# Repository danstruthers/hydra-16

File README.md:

## **Hydra 16**

A multitasking 65C02 computer and its operating system, HydraOS.

The Hydra-16's hardware gives each of 16 tasks its own 32K of RAM, zero page and stack included, with its own RAM and ROM bank selections, so a task switch is one register write.  HydraOS runs on it, Plan 9's way:
* **One kernel** in the BIOS ROM: a preemptive scheduler, one interrupt path, notes, memory and banks, and a jump table made from a specification.  Everything else is a module of the paged ROM, run in place in a task of its own.
* **A base to build on:** the kernel, a serial console driver, the kernel's devices and Woz's monitor are the base (`base/`), which HydraOS is built on and which boots on its own: [write an OS of your own](docs/09-programming/your-own-os.md) on it.
* **Everything a file:** devices are file servers (the console's windows, the disks and HydraFS, sound, GPIO and I2C, the clock, the Vera X, and `/pc`, a folder on the PC over the serial line), and each task has a namespace of its own, built by binds and mounts.
* **Shells and languages:** rc, Plan 9's shell, and the core tools; HyForth (Forth 2012), the login shell; hylang (danlang, a lisp); HyBASIC (QuickBASIC's kind, every number exact); SDKs for C (cc65) and assembly, and `as`, an assembler on the Hydra itself.
* **Tools:** a screen editor (`edit`), a debugger (`db`), a song player that plays ZSM songs and compiles scores as it plays.

The code is built with **cc65** (https://cc65.github.io/), and the board is designed in **KiCad 9** (https://www.kicad.org).

### **Quick start**

```
cd base
node build.js                      the base alone: the kernel, ser, kdev, the monitor (bin/bios_*.bin, bin/prom0.bin)
node sim/run.js -i                 its monitor in your terminal (Ctrl-A x quits)

cd ../reborn
node build.js                      build HydraOS (needs Node.js and cc65): bin/bios_*.bin, bin/prom0.bin ...
node sim/run.js -i                 use the Hydra in your terminal, in the emulator (Ctrl-A x quits)
node sim/web.js                    the emulator in a browser: one file, bin/hydra-16.html, to open (in Git: no
                                   Node.js needed to use it)
node sim/test.js                   the regression tests
```

The ROM images are in Git (`reborn/bin/`) and on each GitHub release, so the chips can be programmed without a toolchain.

### **Documentation**

**[The Hydra-16 book](docs/README.md)** is everything, in order: what the machine is, the board and how to build it
(the parts, the layout, the quirks), the kernel and its calls, the drivers, the shell, the languages, the tools, the
emulator, and the programming guide.  It's also [one PDF](docs/hydra-16.pdf), to print.

| Chapter | |
| :------ | :- |
| [1. The Hydra-16 at a glance](docs/01-overview.md) | The ideas, the software in layers, and a first hour in the emulator |
| [2. The hardware](docs/02-hardware/README.md) | The architecture, the devices, the parts, building it, the layout, the quirks, the cards |
| [3. The base](docs/03-base/README.md) | The boot, the kernel, files and namespaces, the system calls, the monitor |
| [4. The drivers](docs/04-drivers/README.md) | The serial console, the kernel's devices, storage, sound, GPIO, video |
| [5. The shell: rc](docs/05-rc.md) | Plan 9's shell |
| [6. The languages](docs/06-languages/README.md) | HyForth, hylang, HyBASIC, and the numbers they share |
| [7. The tools](docs/07-tools.md) | The core tools, the editors, the debugger, the assembler and disassembler |
| [8. The emulator](docs/08-emulator.md) | The emulator, the build, the tests, the PC tools |
| [9. The programming guide](docs/09-programming/README.md) | Assembly, C, servers and drivers, libraries, your own OS, every system call |

How it was designed, and where it stands: [the plan and the design notes](docs/design/README.md).

### **Repository**

| Folder | What |
| :----- | :--- |
| `base/` | The base: the kernel (the BIOS ROM), the system calls' specification, the console driver `ser`, the kernel's devices `kdev`, the monitor `wozmon`, the assembly SDK's core, the board's emulator and the tests' runner |
| `reborn/` | HydraOS, on the base: its modules, the SDKs, the ROM disk, the SD card's image, its tests |
| `docs/` | The book (its chapters, `docs/build`: the tools that make its parts list, layout drawings, call reference and PDF), and the design notes (`docs/design`) |
| `board/` | KiCad schematics and PCBs: the main board, the memory daughter card, the bus breakout card, the Vera X's glue board |
| `old/` | The old system (the 1.8C line: `os_rom/`, its programs, emulator, build and documents), frozen at HydraOS 1.0; `node old/build.js test` still builds and tests it |

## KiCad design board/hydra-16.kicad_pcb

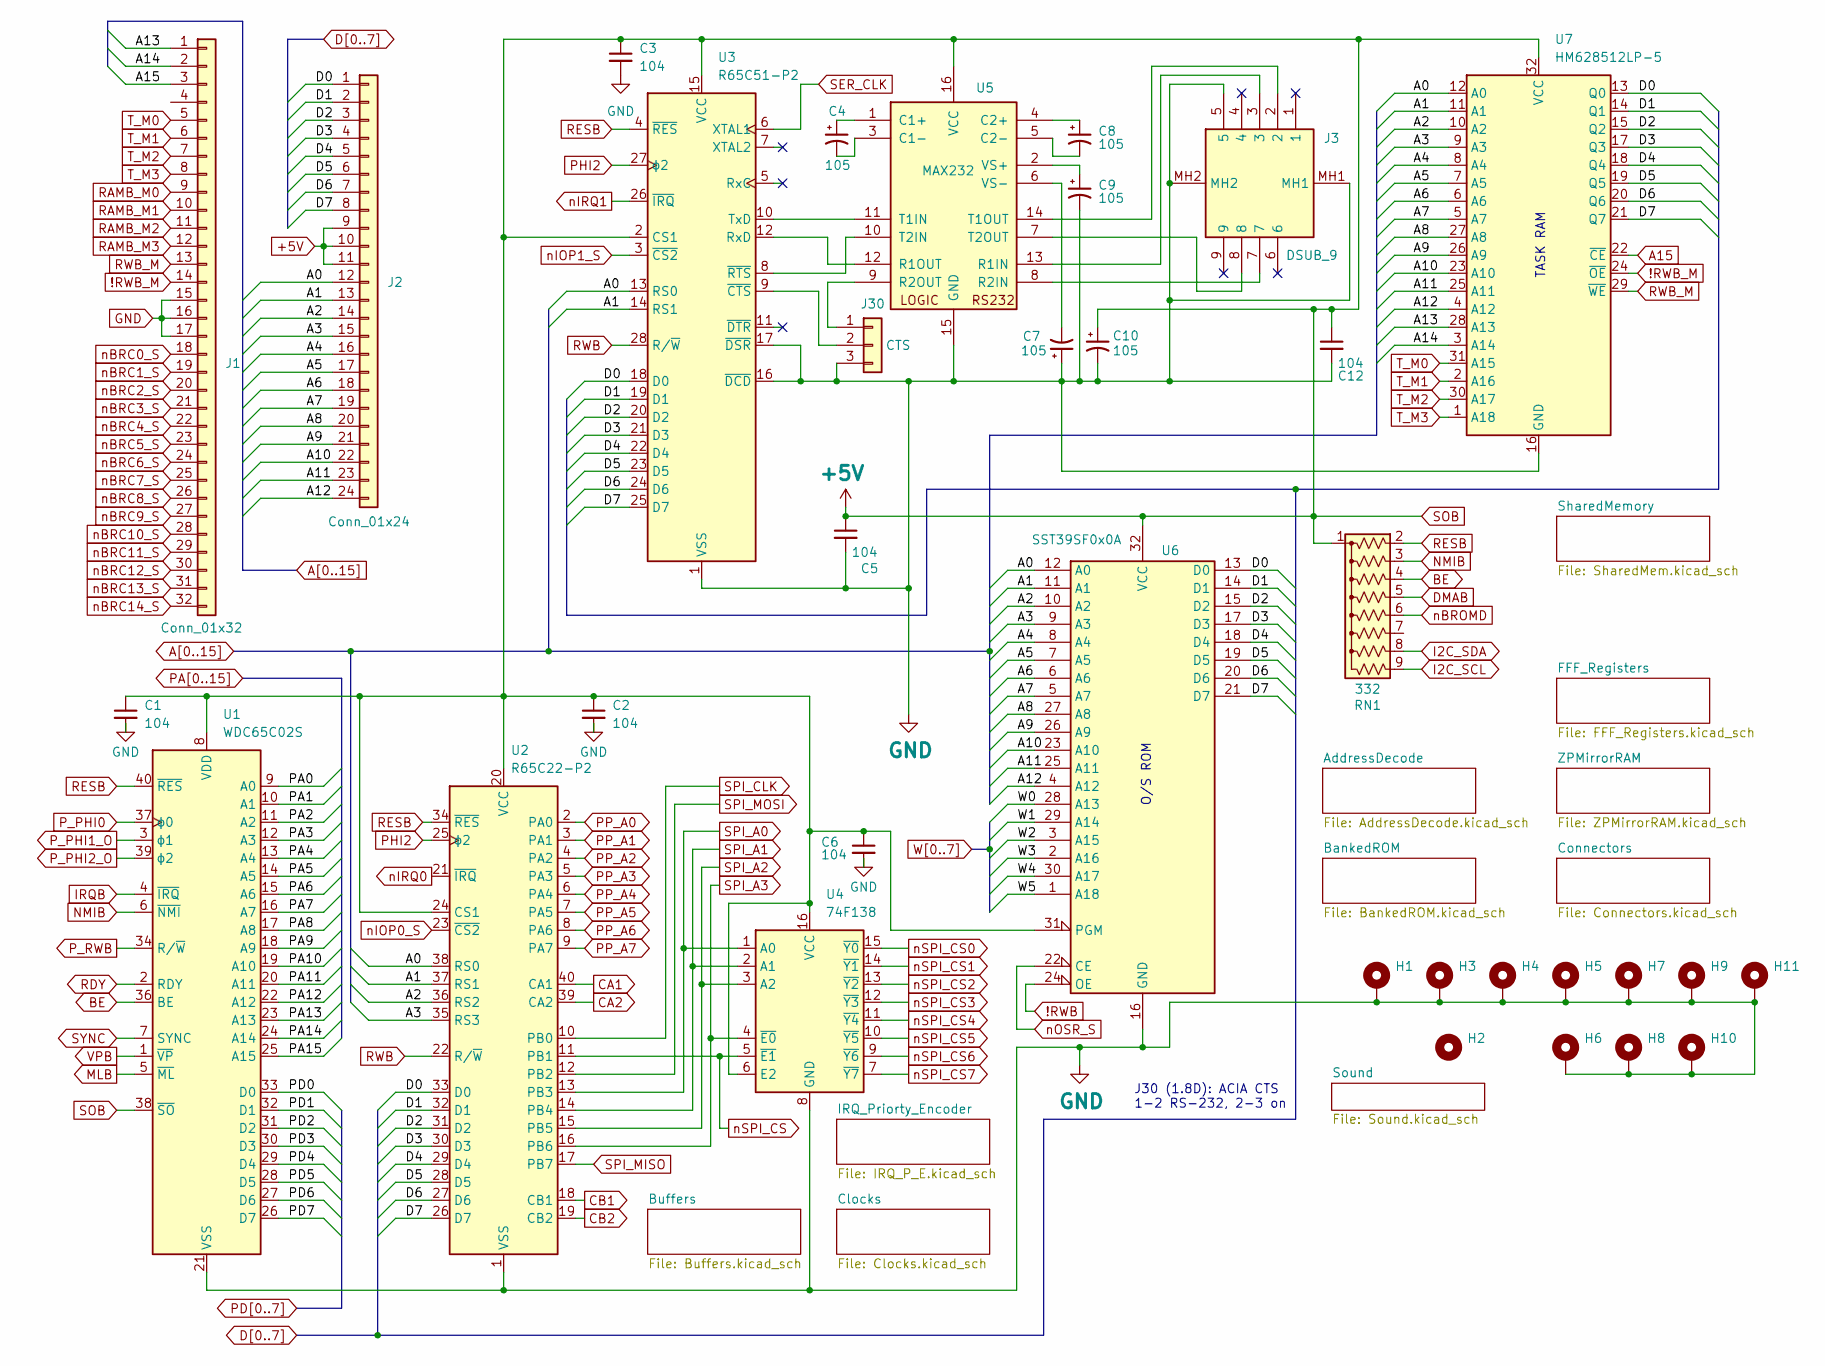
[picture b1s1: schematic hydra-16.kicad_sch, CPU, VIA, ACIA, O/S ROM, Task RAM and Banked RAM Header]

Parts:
C1, C2, C3, C5, C6, C12: 104; C_Disc_D5.0mm_W2.5mm_P5.00mm
C4, C7, C8, C9, C10: 105; C_Disc_D5.0mm_W2.5mm_P2.50mm
H1, H3, H4, H5, H6, H7, H8, H9, H10, H11: MountingHole_Pad; MountingHole_4mm_Pad_TopBottom
H2: MountingHole; MountingHole_4mm
J1: Conn_01x32; PinSocket_1x32_P2.54mm_Vertical
J2: Conn_01x24; PinSocket_1x24_P2.54mm_Vertical
J3: DSUB_9; L77SDE09SA4CH3R; Mouser Part Number 523-L77SDE09SA4CH3R
J30: CTS; PinHeader_1x03_P2.54mm_Vertical
RN1: 332; R_Array_SIP9
U1: WDC65C02S; DIP-40_W15.24mm_Socket_LongPads
U2: R65C22-P2; DIP-40_W15.24mm_Socket_LongPads
U3: R65C51-P2; DIP-28_W15.24mm_Socket_LongPads
U4: 74F138; DIP-16_W7.62mm_Socket_LongPads
U5: MAX232; DIP-16_W7.62mm_Socket_LongPads
U6: SST39SF0x0A; PLCC-32_THT-Socket
U7: HM628512LP-5; DIP-32_W15.24mm_Socket_LongPads

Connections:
!RWB: U6.24 (OE); also elsewhere on the board
!RWB_M: J1.14, U7.24 (~OE); also elsewhere on the board
+5V: C1.1, C2.1, C3.1, C5.1, C6.1, C10.1, C12.1, J2.9, J2.10, J2.11, RN1.1 (common), U1.8 (VDD), U1.38 (~SO), U2.20 (VCC), U2.24 (CS1), U3.2 (CS1), U3.15 (VCC), U4.6 (E2), U4.16 (VCC), U5.16 (VCC), U6.31 (PGM), U6.32 (VCC), U7.32 (VCC); also elsewhere on the board
A0: J2.12, U2.38 (RS0), U3.13 (RS0), U6.12 (A0), U7.12 (A0); also elsewhere on the board
A1: J2.13, U2.37 (RS1), U3.14 (RS1), U6.11 (A1), U7.11 (A1); also elsewhere on the board
A2: J2.14, U2.36 (RS2), U6.10 (A2), U7.10 (A2); also elsewhere on the board
A3: J2.15, U2.35 (RS3), U6.9 (A3), U7.9 (A3); also elsewhere on the board
A4: J2.16, U6.8 (A4), U7.8 (A4); also elsewhere on the board
A5: J2.17, U6.7 (A5), U7.7 (A5); also elsewhere on the board
A6: J2.18, U6.6 (A6), U7.6 (A6); also elsewhere on the board
A7: J2.19, U6.5 (A7), U7.5 (A7); also elsewhere on the board
A8: J2.20, U6.27 (A8), U7.27 (A8); also elsewhere on the board
A9: J2.21, U6.26 (A9), U7.26 (A9); also elsewhere on the board
A10: J2.22, U6.23 (A10), U7.23 (A10); also elsewhere on the board
A11: J2.23, U6.25 (A11), U7.25 (A11); also elsewhere on the board
A12: J2.24, U6.4 (A12), U7.4 (A12); also elsewhere on the board
A13: J1.1, U7.28 (A13); also elsewhere on the board
A14: J1.2, U7.3 (A14); also elsewhere on the board
A15: J1.3, U7.22 (~CE); also elsewhere on the board
BE: RN1.4 (R3), U1.36 (BE); also elsewhere on the board
CA1: U2.40 (CA1); also elsewhere on the board
CA2: U2.39 (CA2); also elsewhere on the board
CB1: U2.18 (CB1)
CB2: U2.19 (CB2)
D0: J2.1, U2.33 (D0), U3.18 (D0), U6.13 (D0), U7.13 (Q0); also elsewhere on the board
D1: J2.2, U2.32 (D1), U3.19 (D1), U6.14 (D1), U7.14 (Q1); also elsewhere on the board
D2: J2.3, U2.31 (D2), U3.20 (D2), U6.15 (D2), U7.15 (Q2); also elsewhere on the board
D3: J2.4, U2.30 (D3), U3.21 (D3), U6.17 (D3), U7.17 (Q3); also elsewhere on the board
D4: J2.5, U2.29 (D4), U3.22 (D4), U6.18 (D4), U7.18 (Q4); also elsewhere on the board
D5: J2.6, U2.28 (D5), U3.23 (D5), U6.19 (D5), U7.19 (Q5); also elsewhere on the board
D6: J2.7, U2.27 (D6), U3.24 (D6), U6.20 (D6), U7.20 (Q6); also elsewhere on the board
D7: J2.8, U2.26 (D7), U3.25 (D7), U6.21 (D7), U7.21 (Q7); also elsewhere on the board
DMAB: RN1.5 (R4); also elsewhere on the board
GND: C1.2, C2.2, C3.2, C5.2, C6.2, C7.1, C9.2, C10.2, C12.2, H1.1, H3.1, H4.1, H5.1, H6.1, H7.1, H8.1, H9.1, H10.1, H11.1, J1.15, J1.16, J1.17, J3.5, J3.MH1, J3.MH2, J30.3, U1.21 (VSS), U2.1 (VSS), U3.1 (VSS), U3.16 (~DCD), U3.17 (~DSR), U4.8 (GND), U5.15 (GND), U6.16 (GND), U7.16 (GND); also elsewhere on the board
I2C_SCL: RN1.9 (R8), U2.2 (PA0); also elsewhere on the board
I2C_SDA: RN1.8 (R7), U2.3 (PA1); also elsewhere on the board
IRQB: U1.4 (~IRQ); also elsewhere on the board
MLB: U1.5 (~ML)
NMIB: RN1.3 (R2), U1.6 (~NMI); also elsewhere on the board
unnamed: J30.1, U5.9 (R2OUT)
unnamed: J30.2, U3.9 (~CTS)
unnamed: U3.12 (RxD), U5.12 (R1OUT)
unnamed: U3.10 (TxD), U5.11 (T1IN)
unnamed: U3.8 (~RTS), U5.10 (T2IN)
unnamed: C4.1, U5.1 (C1+)
unnamed: C4.2, U5.3 (C1-)
unnamed: C8.1, U5.4 (C2+)
unnamed: C8.2, U5.5 (C2-)
unnamed: J3.3, U5.13 (R1IN)
unnamed: J3.7, U5.8 (R2IN)
unnamed: J3.2, U5.14 (T1OUT)
unnamed: J3.8, U5.7 (T2OUT)
unnamed: C9.1, U5.2 (VS+)
unnamed: C7.2, U5.6 (VS-)
PA0: U1.9 (A0); also elsewhere on the board
PA1: U1.10 (A1); also elsewhere on the board
PA2: U1.11 (A2); also elsewhere on the board
PA3: U1.12 (A3); also elsewhere on the board
PA4: U1.13 (A4); also elsewhere on the board
PA5: U1.14 (A5); also elsewhere on the board
PA6: U1.15 (A6); also elsewhere on the board
PA7: U1.16 (A7); also elsewhere on the board
PA8: U1.17 (A8); also elsewhere on the board
PA9: U1.18 (A9); also elsewhere on the board
PA10: U1.19 (A10); also elsewhere on the board
PA11: U1.20 (A11); also elsewhere on the board
PA12: U1.22 (A12); also elsewhere on the board
PA13: U1.23 (A13); also elsewhere on the board
PA14: U1.24 (A14); also elsewhere on the board
PA15: U1.25 (A15); also elsewhere on the board
PD0: U1.33 (D0); also elsewhere on the board
PD1: U1.32 (D1); also elsewhere on the board
PD2: U1.31 (D2); also elsewhere on the board
PD3: U1.30 (D3); also elsewhere on the board
PD4: U1.29 (D4); also elsewhere on the board
PD5: U1.28 (D5); also elsewhere on the board
PD6: U1.27 (D6); also elsewhere on the board
PD7: U1.26 (D7); also elsewhere on the board
PHI2: U2.25 (ϕ2), U3.27 (ϕ2); also elsewhere on the board
PP_A2: U2.4 (PA2); also elsewhere on the board
PP_A3: U2.5 (PA3); also elsewhere on the board
PP_A4: U2.6 (PA4); also elsewhere on the board
PP_A5: U2.7 (PA5); also elsewhere on the board
PP_A6: U2.8 (PA6); also elsewhere on the board
PP_A7: U2.9 (PA7); also elsewhere on the board
P_PHI0: U1.37 (ϕ0); also elsewhere on the board
P_PHI1_O: U1.3 (ϕ1)
P_PHI2_O: U1.39 (ϕ2)
P_RWB: U1.34 (R/~W); also elsewhere on the board
RAMB_M0: J1.9; also elsewhere on the board
RAMB_M1: J1.10; also elsewhere on the board
RAMB_M2: J1.11; also elsewhere on the board
RAMB_M3: J1.12; also elsewhere on the board
RDY: U1.2 (RDY); also elsewhere on the board
RESB: RN1.2 (R1), U1.40 (~RES), U2.34 (~RES), U3.4 (~RES); also elsewhere on the board
RWB: U2.22 (R/~W), U3.28 (R/~W); also elsewhere on the board
RWB_M: J1.13, U7.29 (~WE); also elsewhere on the board
SER_CLK: U3.6 (XTAL1); also elsewhere on the board
SPI_A0: U2.13 (PB3), U4.1 (A0); also elsewhere on the board
SPI_A1: U2.14 (PB4), U4.2 (A1); also elsewhere on the board
SPI_A2: U2.15 (PB5), U4.3 (A2); also elsewhere on the board
SPI_A3: U2.16 (PB6), U4.4 (~E0); also elsewhere on the board
SPI_CLK: U2.10 (PB0); also elsewhere on the board
SPI_MISO: U2.17 (PB7); also elsewhere on the board
SPI_MOSI: U2.12 (PB2); also elsewhere on the board
SYNC: U1.7 (SYNC); also elsewhere on the board
T_M0: J1.5, U7.31 (A15); also elsewhere on the board
T_M1: J1.6, U7.2 (A16); also elsewhere on the board
T_M2: J1.7, U7.30 (A17); also elsewhere on the board
T_M3: J1.8, U7.1 (A18); also elsewhere on the board
VPB: U1.1 (~VP)
W0: U6.28 (A13); also elsewhere on the board
W1: U6.29 (A14); also elsewhere on the board
W2: U6.3 (A15); also elsewhere on the board
W3: U6.2 (A16); also elsewhere on the board
W4: U6.30 (A17); also elsewhere on the board
W5: U6.1 (A18); also elsewhere on the board
nBRC0_S: J1.18; also elsewhere on the board
nBRC1_S: J1.19; also elsewhere on the board
nBRC2_S: J1.20; also elsewhere on the board
nBRC3_S: J1.21; also elsewhere on the board
nBRC4_S: J1.22; also elsewhere on the board
nBRC5_S: J1.23; also elsewhere on the board
nBRC6_S: J1.24; also elsewhere on the board
nBRC7_S: J1.25; also elsewhere on the board
nBRC8_S: J1.26; also elsewhere on the board
nBRC9_S: J1.27; also elsewhere on the board
nBRC10_S: J1.28; also elsewhere on the board
nBRC11_S: J1.29; also elsewhere on the board
nBRC12_S: J1.30; also elsewhere on the board
nBRC13_S: J1.31; also elsewhere on the board
nBRC14_S: J1.32; also elsewhere on the board
nBROMD: RN1.6 (R5); also elsewhere on the board
nIOP0_S: U2.23 (~CS2); also elsewhere on the board
nIOP1_S: U3.3 (~CS2); also elsewhere on the board
nIRQ0: U2.21 (~IRQ); also elsewhere on the board
nIRQ1: U3.26 (~IRQ); also elsewhere on the board
nOSR_S: U6.22 (CE); also elsewhere on the board
nSPI_CS: U2.11 (PB1), U4.5 (~E1); also elsewhere on the board
nSPI_CS0: U4.15 (~Y0); also elsewhere on the board
nSPI_CS1: U4.14 (~Y1); also elsewhere on the board
nSPI_CS2: U4.13 (~Y2); also elsewhere on the board
nSPI_CS3: U4.12 (~Y3); also elsewhere on the board
nSPI_CS4: U4.11 (~Y4); also elsewhere on the board
nSPI_CS5: U4.10 (~Y5); also elsewhere on the board
nSPI_CS6: U4.9 (~Y6); also elsewhere on the board
nSPI_CS7: U4.7 (~Y7); also elsewhere on the board

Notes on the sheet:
TASK RAM
O/S ROM
J30 (1.8D): ACIA CTS 1-2 RS-232, 2-3 on

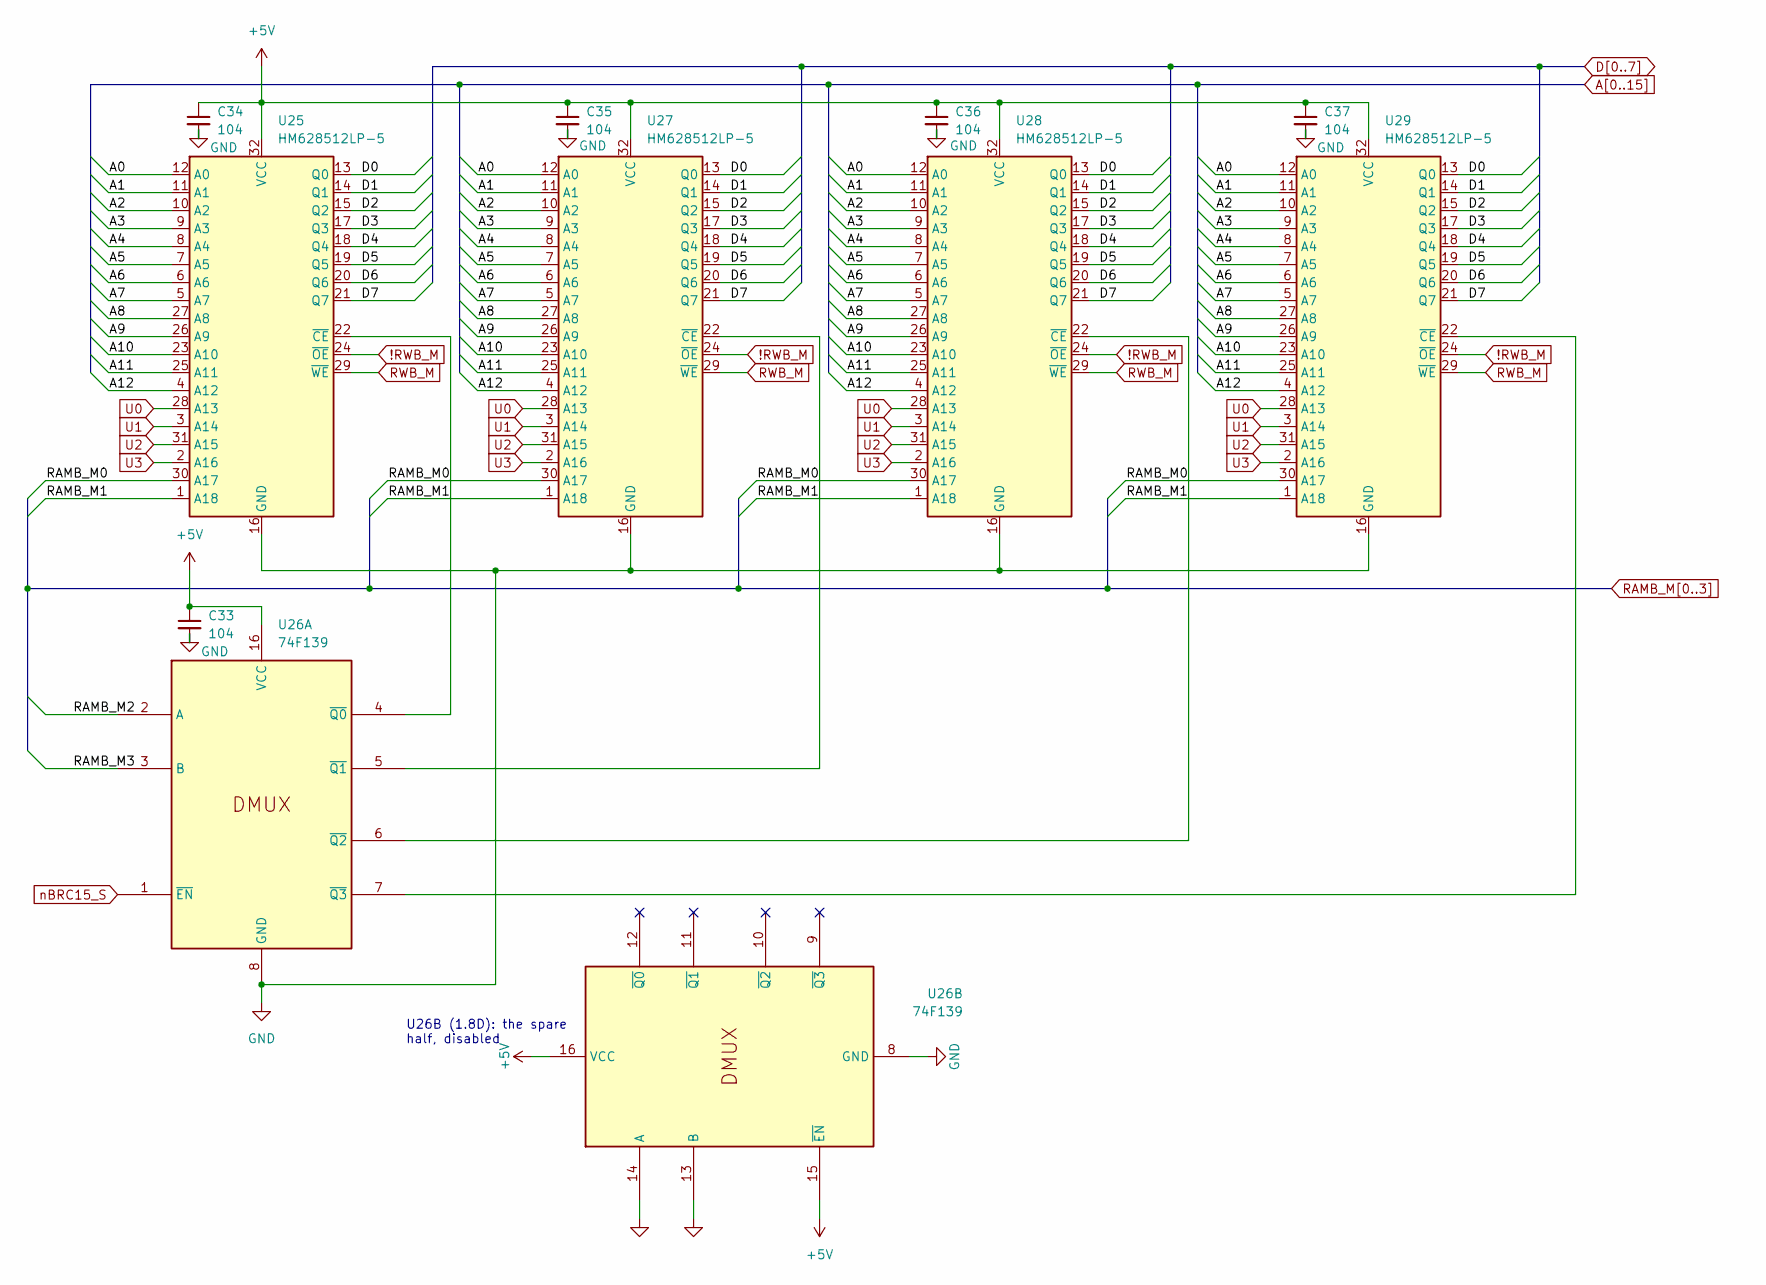
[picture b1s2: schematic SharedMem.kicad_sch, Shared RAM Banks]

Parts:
C33, C34, C35, C36, C37: 104; C_Disc_D5.0mm_W2.5mm_P5.00mm
U25, U27, U28, U29: HM628512LP-5; SOP-32_11.305x20.495mm_P1.27mm
U26: 74F139; DIP-16_W7.62mm_Socket_LongPads

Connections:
!RWB_M: U25.24 (~OE), U27.24 (~OE), U28.24 (~OE), U29.24 (~OE); also elsewhere on the board
+5V: C33.1, C34.1, C35.1, C36.1, C37.1, U25.32 (VCC), U26.15 (~EN), U26.16 (VCC), U27.32 (VCC), U28.32 (VCC), U29.32 (VCC); also elsewhere on the board
A0: U25.12 (A0), U27.12 (A0), U28.12 (A0), U29.12 (A0); also elsewhere on the board
A1: U25.11 (A1), U27.11 (A1), U28.11 (A1), U29.11 (A1); also elsewhere on the board
A2: U25.10 (A2), U27.10 (A2), U28.10 (A2), U29.10 (A2); also elsewhere on the board
A3: U25.9 (A3), U27.9 (A3), U28.9 (A3), U29.9 (A3); also elsewhere on the board
A4: U25.8 (A4), U27.8 (A4), U28.8 (A4), U29.8 (A4); also elsewhere on the board
A5: U25.7 (A5), U27.7 (A5), U28.7 (A5), U29.7 (A5); also elsewhere on the board
A6: U25.6 (A6), U27.6 (A6), U28.6 (A6), U29.6 (A6); also elsewhere on the board
A7: U25.5 (A7), U27.5 (A7), U28.5 (A7), U29.5 (A7); also elsewhere on the board
A8: U25.27 (A8), U27.27 (A8), U28.27 (A8), U29.27 (A8); also elsewhere on the board
A9: U25.26 (A9), U27.26 (A9), U28.26 (A9), U29.26 (A9); also elsewhere on the board
A10: U25.23 (A10), U27.23 (A10), U28.23 (A10), U29.23 (A10); also elsewhere on the board
A11: U25.25 (A11), U27.25 (A11), U28.25 (A11), U29.25 (A11); also elsewhere on the board
A12: U25.4 (A12), U27.4 (A12), U28.4 (A12), U29.4 (A12); also elsewhere on the board
D0: U25.13 (Q0), U27.13 (Q0), U28.13 (Q0), U29.13 (Q0); also elsewhere on the board
D1: U25.14 (Q1), U27.14 (Q1), U28.14 (Q1), U29.14 (Q1); also elsewhere on the board
D2: U25.15 (Q2), U27.15 (Q2), U28.15 (Q2), U29.15 (Q2); also elsewhere on the board
D3: U25.17 (Q3), U27.17 (Q3), U28.17 (Q3), U29.17 (Q3); also elsewhere on the board
D4: U25.18 (Q4), U27.18 (Q4), U28.18 (Q4), U29.18 (Q4); also elsewhere on the board
D5: U25.19 (Q5), U27.19 (Q5), U28.19 (Q5), U29.19 (Q5); also elsewhere on the board
D6: U25.20 (Q6), U27.20 (Q6), U28.20 (Q6), U29.20 (Q6); also elsewhere on the board
D7: U25.21 (Q7), U27.21 (Q7), U28.21 (Q7), U29.21 (Q7); also elsewhere on the board
GND: C33.2, C34.2, C35.2, C36.2, C37.2, U25.16 (GND), U26.8 (GND), U26.13 (B), U26.14 (A), U27.16 (GND), U28.16 (GND), U29.16 (GND); also elsewhere on the board
unnamed: U25.22 (~CE), U26.4 (~Q0)
unnamed: U26.5 (~Q1), U27.22 (~CE)
unnamed: U26.6 (~Q2), U28.22 (~CE)
unnamed: U26.7 (~Q3), U29.22 (~CE)
RAMB_M0: U25.30 (A17), U27.30 (A17), U28.30 (A17), U29.30 (A17); also elsewhere on the board
RAMB_M1: U25.1 (A18), U27.1 (A18), U28.1 (A18), U29.1 (A18); also elsewhere on the board
RAMB_M2: U26.2 (A); also elsewhere on the board
RAMB_M3: U26.3 (B); also elsewhere on the board
RWB_M: U25.29 (~WE), U27.29 (~WE), U28.29 (~WE), U29.29 (~WE); also elsewhere on the board
U0: U25.28 (A13), U27.28 (A13), U28.28 (A13), U29.28 (A13); also elsewhere on the board
U1: U25.3 (A14), U27.3 (A14), U28.3 (A14), U29.3 (A14); also elsewhere on the board
U2: U25.31 (A15), U27.31 (A15), U28.31 (A15), U29.31 (A15); also elsewhere on the board
U3: U25.2 (A16), U27.2 (A16), U28.2 (A16), U29.2 (A16); also elsewhere on the board
nBRC15_S: U26.1 (~EN); also elsewhere on the board

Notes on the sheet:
U26B (1.8D): the spare half, disabled

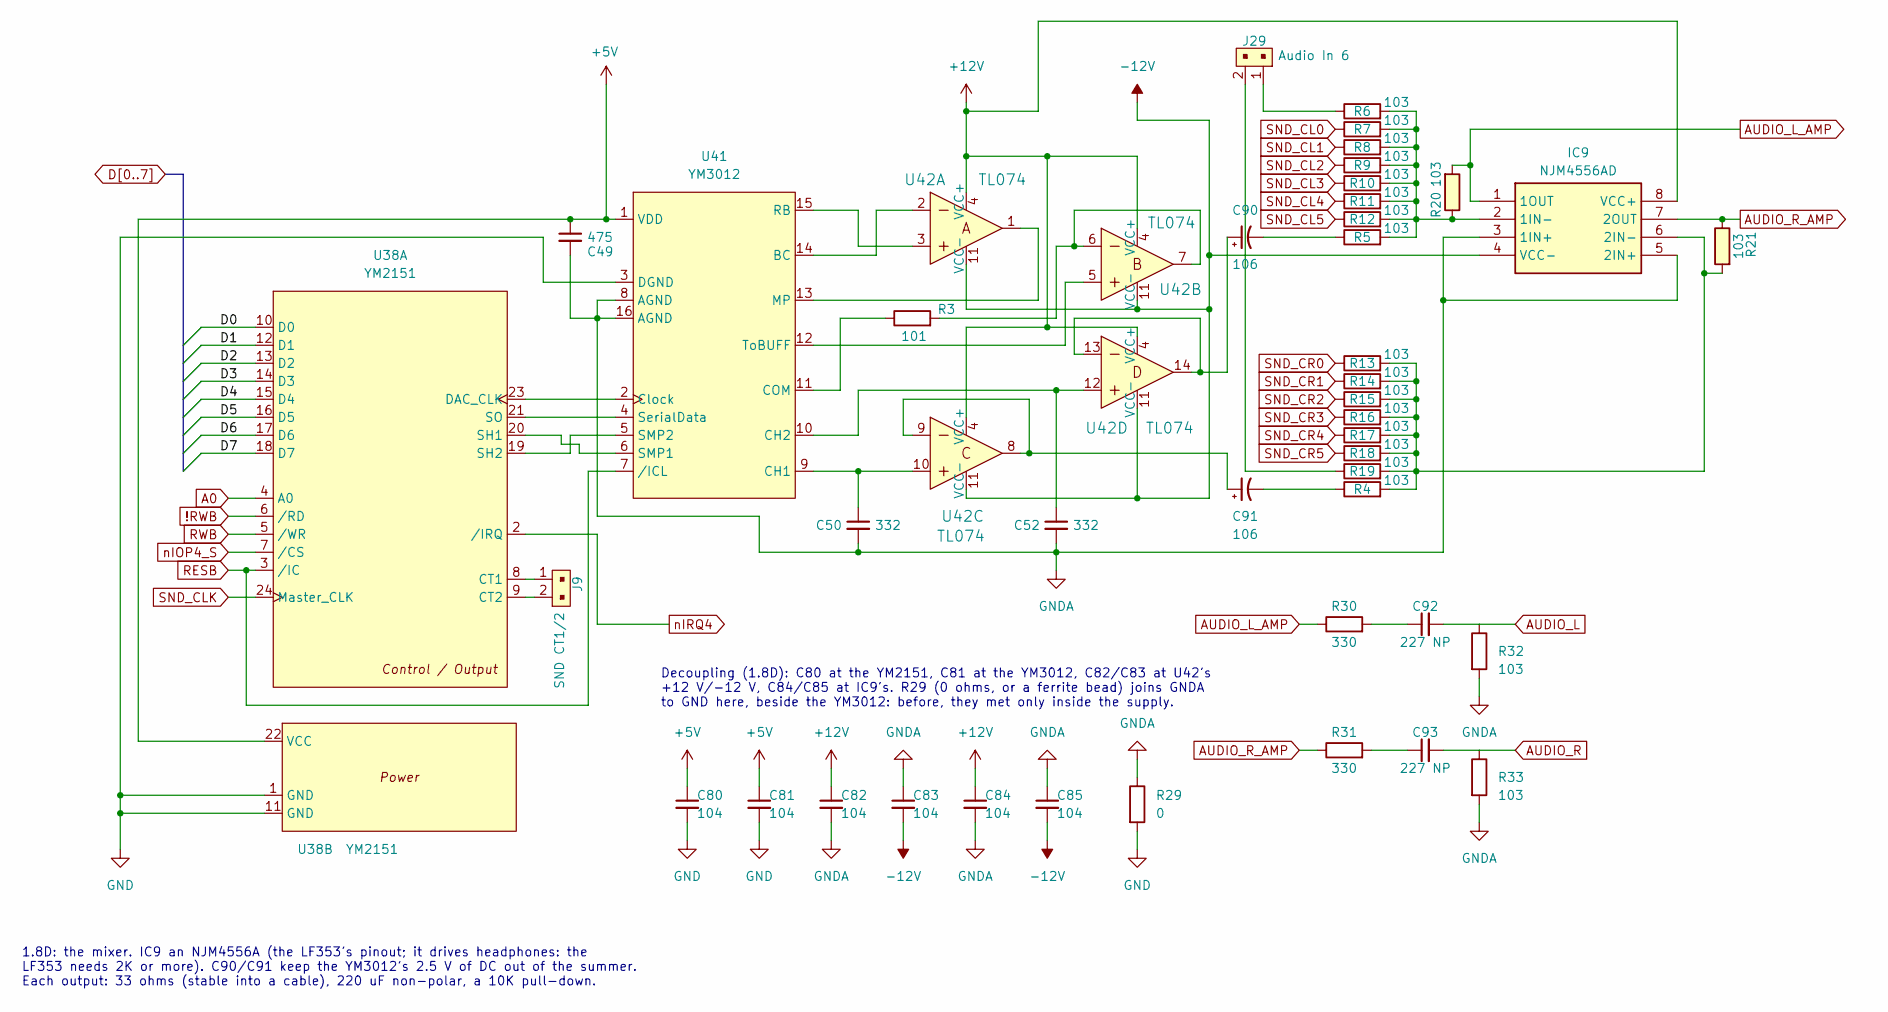
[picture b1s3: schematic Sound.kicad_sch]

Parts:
C49: 475; C_Disc_D5.0mm_W2.5mm_P2.50mm
C50, C52: 332; C_Disc_D5.0mm_W2.5mm_P2.50mm
C80, C81, C82, C83, C84, C85: 104; C_Disc_D5.0mm_W2.5mm_P5.00mm
C90, C91: 106; CP_Radial_D5.0mm_P2.50mm
C92, C93: 227 NP; CP_Radial_D8.0mm_P3.50mm
IC9: NJM4556AD; DIP-8_W7.62mm_Socket_LongPads; Mouser Part Number 595-LF353P
J9: SND CT1/2; PinHeader_2x01_P2.54mm_Vertical; MPN 22-23-2021; Digi-Key_PN WM4200-ND
J29: Audio In 6; PinHeader_2x01_P2.54mm_Vertical; MPN 22-23-2021; Digi-Key_PN WM4200-ND
R3: 101; R_Axial_DIN0204_L3.6mm_D1.6mm_P5.08mm_Horizontal
R4, R5, R6, R7, R8, R9, R10, R11, R12, R13, R14, R15, R16, R17, R18, R19, R20, R21: 103; R_Axial_DIN0204_L3.6mm_D1.6mm_P5.08mm_Horizontal
R29: 0; R_Axial_DIN0207_L6.3mm_D2.5mm_P10.16mm_Horizontal
R30, R31: 330; R_Axial_DIN0207_L6.3mm_D2.5mm_P10.16mm_Horizontal
R32, R33: 103; R_Axial_DIN0207_L6.3mm_D2.5mm_P10.16mm_Horizontal
U38: YM2151; DIP-24_W15.24mm_Socket_LongPads
U41: YM3012; DIP-16_W7.62mm_Socket_LongPads
U42: TL074; DIP-14_W7.62mm_Socket_LongPads; MPN TL074CN; Digi-Key_PN 296-1777-ND

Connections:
!RWB: U38.6 (/RD); also elsewhere on the board
+5V: C49.1, C80.1, C81.1, U38.22 (VCC), U41.1 (VDD); also elsewhere on the board
+12V: C82.1, C84.1, IC9.8 (VCC+), U42.4 (VCC+); also elsewhere on the board
-12V: C83.2, C85.2, IC9.4 (VCC-), U42.11 (VCC-); also elsewhere on the board
A0: U38.4 (A0); also elsewhere on the board
AUDIO_L: C92.2, R32.1; also elsewhere on the board
AUDIO_L_AMP: IC9.1 (1OUT), R20.1, R30.1
AUDIO_R: C93.2, R33.1; also elsewhere on the board
AUDIO_R_AMP: IC9.7 (2OUT), R21.2, R31.1
D0: U38.10 (D0); also elsewhere on the board
D1: U38.12 (D1); also elsewhere on the board
D2: U38.13 (D2); also elsewhere on the board
D3: U38.14 (D3); also elsewhere on the board
D4: U38.15 (D4); also elsewhere on the board
D5: U38.16 (D5); also elsewhere on the board
D6: U38.17 (D6); also elsewhere on the board
D7: U38.18 (D7); also elsewhere on the board
GND: C80.2, C81.2, R29.2, U38.1 (GND), U38.11 (GND), U41.3 (DGND); also elsewhere on the board
GNDA: C49.2, C50.2, C52.2, C82.2, C83.1, C84.2, C85.1, IC9.3 (1IN+), IC9.5 (2IN+), R29.1, R32.2, R33.2, U41.8 (AGND), U41.16 (AGND); also elsewhere on the board
unnamed: C90.1, U42.13, U42.14
unnamed: C90.2, R5.1
unnamed: C91.1, U42.8, U42.9
unnamed: C91.2, R4.1
unnamed: C92.1, R30.2
unnamed: C93.1, R31.2
unnamed: IC9.2 (1IN-), R5.2, R6.2, R7.2, R8.2, R9.2, R10.2, R11.2, R12.2, R20.2
unnamed: IC9.6 (2IN-), R4.2, R13.2, R14.2, R15.2, R16.2, R17.2, R18.2, R19.2, R21.1
unnamed: J29.1, R6.1
unnamed: J29.2, R19.1
unnamed: R3.2, U42.6, U42.7
unnamed: J9.1, U38.8 (CT1)
unnamed: J9.2, U38.9 (CT2)
unnamed: U38.23 (DAC_CLK), U41.2 (Clock)
unnamed: U38.20 (SH1), U41.6 (SMP1)
unnamed: U38.19 (SH2), U41.5 (SMP2)
unnamed: U38.21 (SO), U41.4 (SerialData)
unnamed: U41.14 (BC), U42.2
unnamed: C50.1, U41.9 (CH1), U42.10
unnamed: C52.1, U41.10 (CH2), U42.12
unnamed: R3.1, U41.11 (COM)
unnamed: U41.13 (MP), U42.1
unnamed: U41.15 (RB), U42.3
unnamed: U41.12 (ToBUFF), U42.5
RESB: U38.3 (/IC), U41.7 (/ICL); also elsewhere on the board
RWB: U38.5 (/WR); also elsewhere on the board
SND_CL0: R7.1; also elsewhere on the board
SND_CLK: U38.24 (Master_CLK); also elsewhere on the board
SND_CR0: R13.1; also elsewhere on the board
nIOP4_S: U38.7 (/CS); also elsewhere on the board
nIRQ4: U38.2 (/IRQ); also elsewhere on the board

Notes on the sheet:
Decoupling (1.8D): C80 at the YM2151, C81 at the YM3012, C82/C83 at U42's +12 V/-12 V, C84/C85 at IC9's. R29 (0 ohms, or a ferrite bead) joins GNDA to GND here, beside the YM3012: before, they met only inside the supply.
1.8D: the mixer. IC9 an NJM4556A (the LF353's pinout; it drives headphones: the LF353 needs 2K or more). C90/C91 keep the YM3012's 2.5 V of DC out of the summer. Each output: 33 ohms (stable into a cable), 220 uF non-polar, a 10K pull-down.

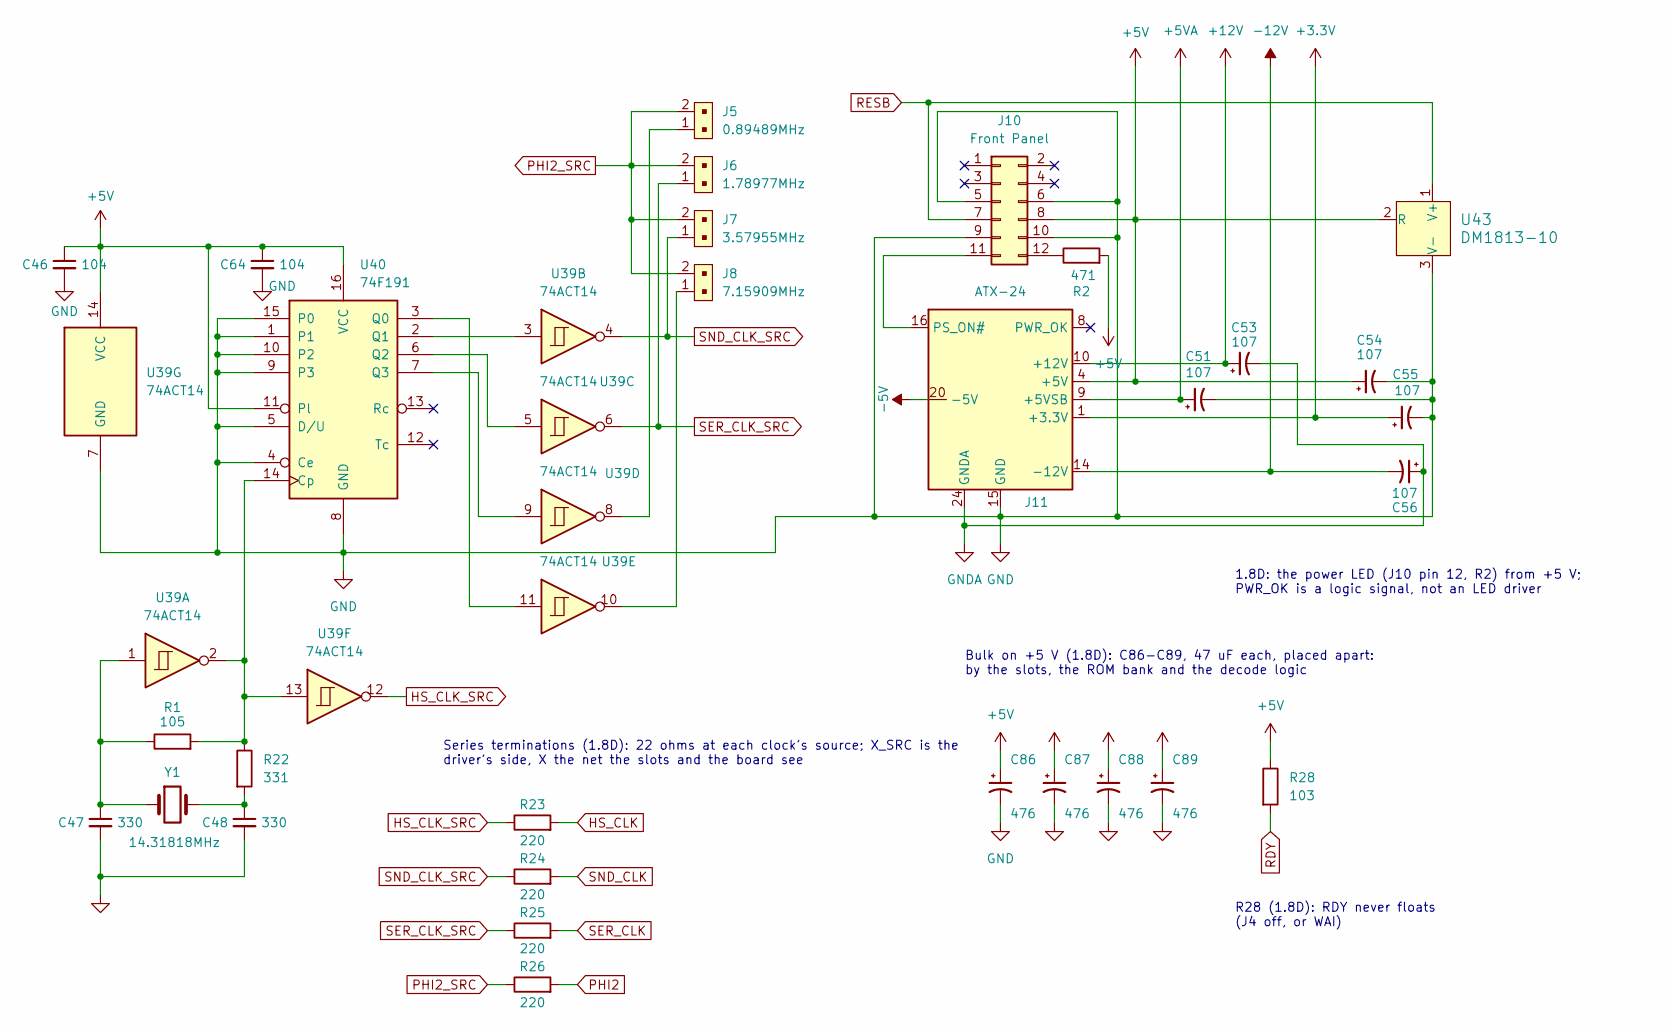
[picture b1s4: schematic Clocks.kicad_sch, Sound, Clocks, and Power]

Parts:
C46, C64: 104; C_Disc_D5.0mm_W2.5mm_P5.00mm
C47, C48: 330; C_Disc_D5.0mm_W2.5mm_P2.50mm
C51, C53, C54, C55, C56: 107; CP_Radial_D6.3mm_P2.50mm
C86, C87, C88, C89: 476; CP_Radial_D6.3mm_P2.50mm
J5: 0.89489MHz; PinHeader_2x01_P2.54mm_Vertical; MPN 22-23-2021; Digi-Key_PN WM4200-ND
J6: 1.78977MHz; PinHeader_2x01_P2.54mm_Vertical; MPN 22-23-2021; Digi-Key_PN WM4200-ND
J7: 3.57955MHz; PinHeader_2x01_P2.54mm_Vertical; MPN 22-23-2021; Digi-Key_PN WM4200-ND
J8: 7.15909MHz; PinHeader_2x01_P2.54mm_Vertical; MPN 22-23-2021; Digi-Key_PN WM4200-ND
J10: Front Panel; PinHeader_2x06_P2.54mm_Vertical
J11: ATX-24; Molex_Mini-Fit_Jr_5566-24A2_2x12_P4.20mm_Vertical
R1: 105; R_Axial_DIN0204_L3.6mm_D1.6mm_P5.08mm_Horizontal
R2: 471; R_Axial_DIN0204_L3.6mm_D1.6mm_P5.08mm_Horizontal
R22: 331; R_Axial_DIN0204_L3.6mm_D1.6mm_P5.08mm_Horizontal
R23, R24, R25, R26: 220; R_Axial_DIN0204_L3.6mm_D1.6mm_P5.08mm_Horizontal
R28: 103; R_Axial_DIN0204_L3.6mm_D1.6mm_P5.08mm_Horizontal
U39: 74ACT14; DIP-14_W7.62mm_Socket_LongPads
U40: 74F191; DIP-16_W7.62mm_Socket_LongPads
U43: DM1813-10; TO-92_Inline_Wide; MPN LM334Z/NOPB; Digi-Key_PN LM334ZNS/NOPB-ND
Y1: 14.31818MHz; Crystal_HC18-U_Vertical

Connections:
+3.3V: C55.1, J11.1 (+3.3V), J11.2 (+3.3V), J11.12 (+3.3V), J11.13 (+3.3V)
+5V: C46.1, C54.1, C64.1, C86.1, C87.1, C88.1, C89.1, J10.8, J11.4 (+5V), J11.6 (+5V), J11.21 (+5V), J11.22 (+5V), J11.23 (+5V), R2.2, R28.1, U39.14 (VCC), U40.11 (Pl), U40.16 (VCC), U43.2 (R); also elsewhere on the board
+5VA: C51.1, J11.9 (+5VSB)
+12V: C53.1, J11.10 (+12V), J11.11 (+12V); also elsewhere on the board
-5V: J11.20 (-5V); also elsewhere on the board
-12V: C56.2, J11.14 (-12V); also elsewhere on the board
GND: C46.2, C47.2, C48.2, C51.2, C54.2, C55.2, C64.2, C86.2, C87.2, C88.2, C89.2, J10.5, J10.6, J10.9, J10.10, J11.3 (GND), J11.5 (GND), J11.7 (GND), J11.15 (GND), J11.17 (GND), J11.18 (GND), J11.19 (GND), U39.7 (GND), U40.1, U40.4 (Ce), U40.5 (D/U), U40.8 (GND), U40.9 (P3), U40.10 (P2), U40.15 (P0), U43.3 (V-); also elsewhere on the board
GNDA: C53.2, C56.1, J11.24 (GNDA); also elsewhere on the board
HS_CLK: R23.2; also elsewhere on the board
HS_CLK_SRC: R23.1, U39.12
unnamed: C47.1, R1.1, U39.1, Y1.1
unnamed: C48.1, R22.2, Y1.2
unnamed: J5.1, U39.8
unnamed: J8.1, U39.10
unnamed: J10.11, J11.16 (PS_ON#)
unnamed: J10.12, R2.1
unnamed: R1.2, R22.1, U39.2, U39.13, U40.14 (Cp)
unnamed: U39.11, U40.3 (Q0)
unnamed: U39.3, U40.2 (Q1)
unnamed: U39.5, U40.6 (Q2)
unnamed: U39.9, U40.7 (Q3)
PHI2: R26.2; also elsewhere on the board
PHI2_SRC: J5.2, J6.2, J7.2, J8.2, R26.1
RDY: R28.2; also elsewhere on the board
RESB: J10.7, U43.1 (V+); also elsewhere on the board
SER_CLK: R25.2; also elsewhere on the board
SER_CLK_SRC: J6.1, R25.1, U39.6
SND_CLK: R24.2; also elsewhere on the board
SND_CLK_SRC: J7.1, R24.1, U39.4

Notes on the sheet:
R28 (1.8D): RDY never floats (J4 off, or WAI)
Bulk on +5 V (1.8D): C86-C89, 47 uF each, placed apart: by the slots, the ROM bank and the decode logic
Series terminations (1.8D): 22 ohms at each clock's source; X_SRC is the driver's side, X the net the slots and the board see
1.8D: the power LED (J10 pin 12, R2) from +5 V; PWR_OK is a logic signal, not an LED driver
